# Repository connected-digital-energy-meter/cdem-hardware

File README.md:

# Connected Digital Energy Meter - Hardware

TODO

## Gerber and BOM

Checkout following guides:

* [How to generate Gerber and Drill files in KiCad 5](https://support.jlcpcb.com/article/149-how-to-generate-gerber-and-drill-files-in-kicad)
* [How to generate the BOM and Centroid file from KiCAD](https://support.jlcpcb.com/article/84-how-to-generate-the-bom-and-centroid-file-from-kicad)

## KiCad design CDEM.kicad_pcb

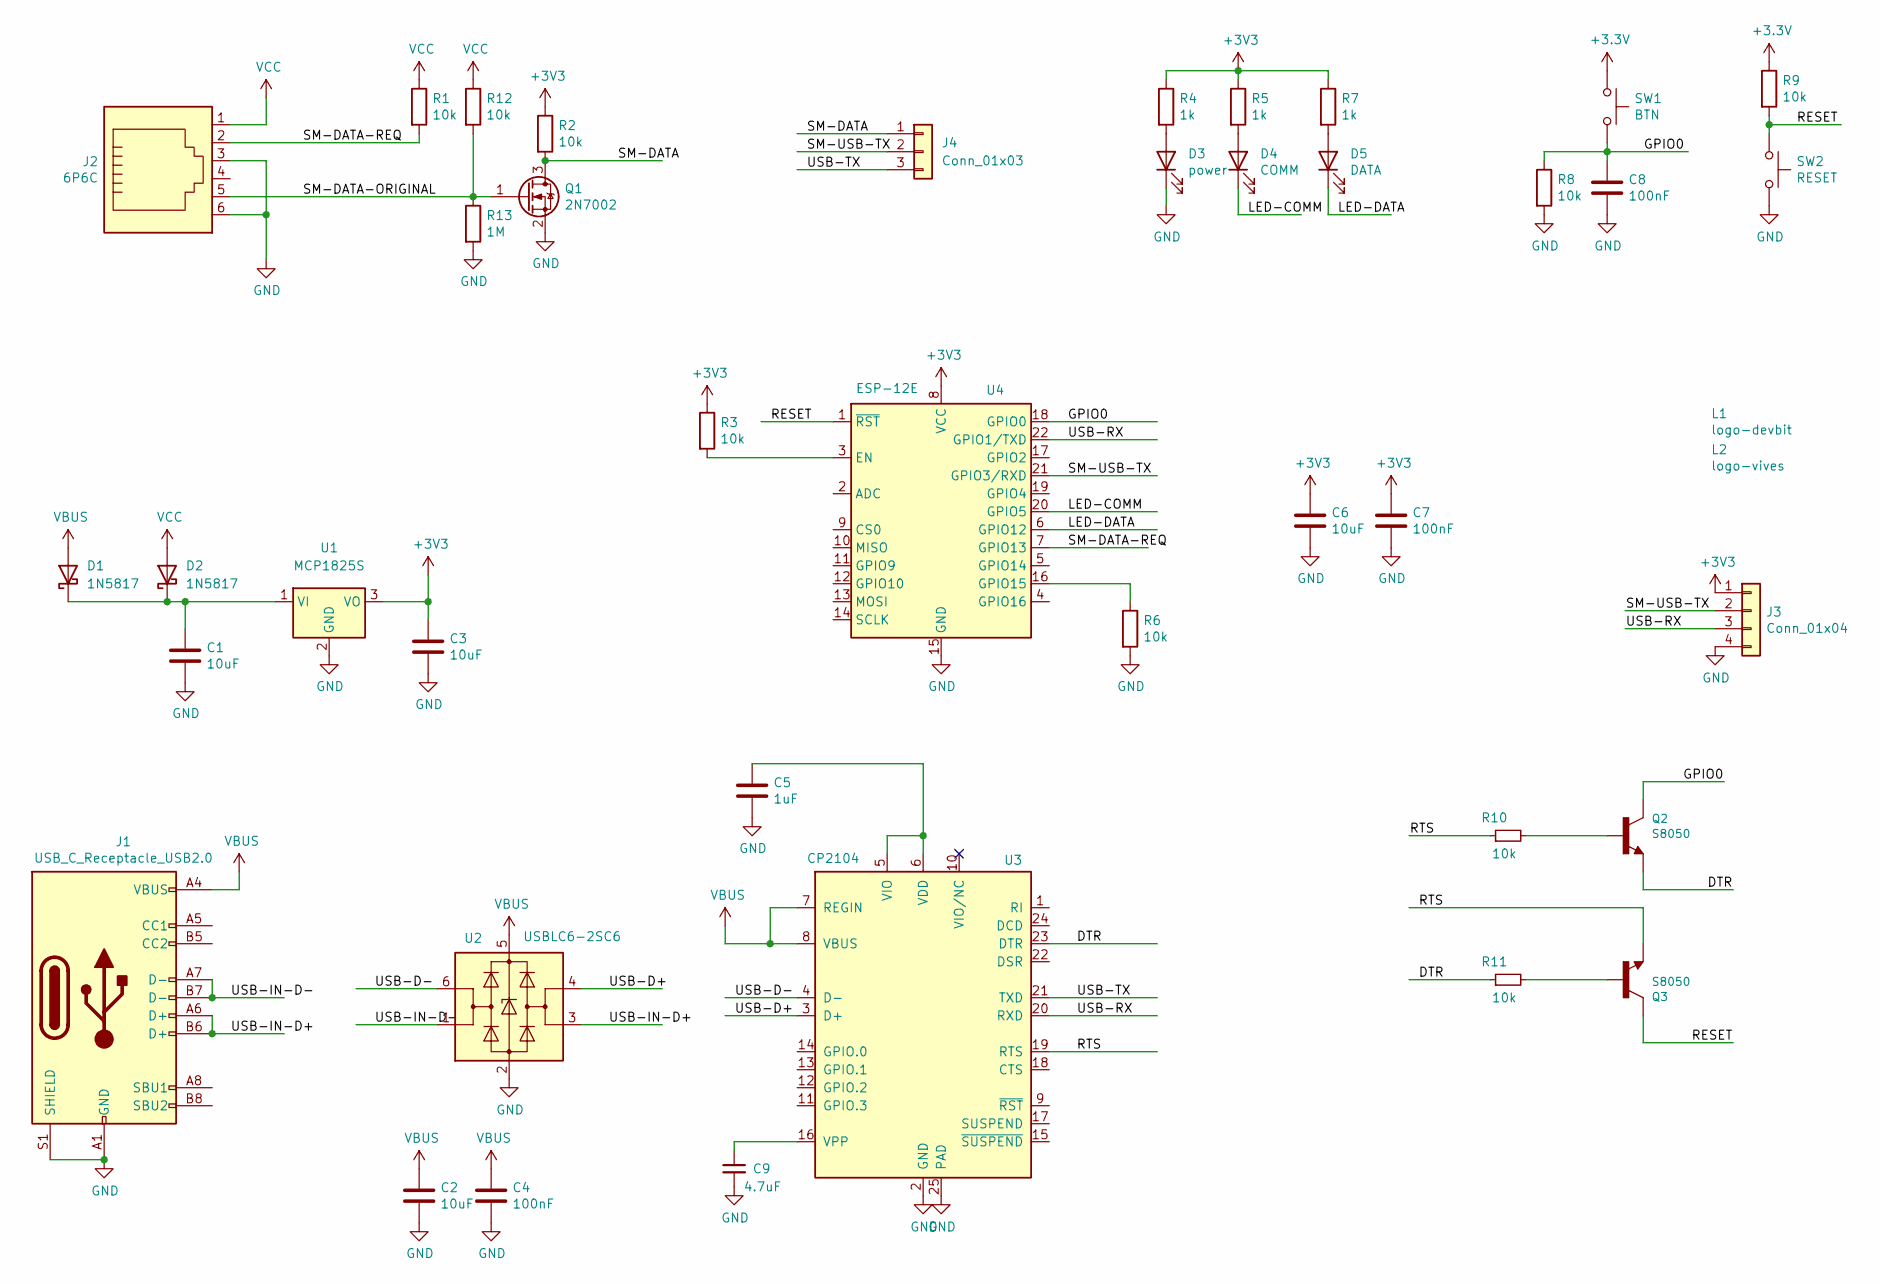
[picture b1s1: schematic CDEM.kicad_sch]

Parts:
C1, C2, C3, C6: 10uF; C_0805_2012Metric; LCSC C15850
C4, C7, C8: 100nF; C_0603_1608Metric; LCSC C14663
C5: 1uF; C_0603_1608Metric; LCSC C15849
C9: 4.7uF; C_0805_2012Metric; LCSC C1779
D1, D2: 1N5817; D_SOD-123; LCSC C727113
D3: power; LED_0603_1608Metric; LCSC C72041
D4: COMM; LED_0603_1608Metric; LCSC C72043
D5: DATA; LED_0603_1608Metric; LCSC C72038
J1: USB_C_Receptacle_USB2.0; USB_C_Receptacle_HRO_TYPE-C-31-M-12; LCSC C165948
J2: 6P6C; RJ12_Amphenol_54601; LCSC C305981
J3: Conn_01x04; PinHeader_1x04_P2.54mm_Vertical
J4: Conn_01x03; PinHeader_1x03_P2.54mm_Vertical; LCSC C390679
L1: logo-devbit; logo_devbit_8mm
L2: logo-vives; logo_vives_10mm
Q1: 2N7002; SOT-23; LCSC C8545
Q2, Q3: S8050; SOT-23; LCSC C2146
R1, R2, R3, R6, R8, R9, R10, R11, R12: 10k; R_0603_1608Metric; LCSC C25804
R4, R5, R7: 1k; R_0603_1608Metric; LCSC C21190
R13: 1M; R_0603_1608Metric; LCSC C17514
SW1: BTN; SW_SPST_B3U-1000P; LCSC C231329
SW2: RESET; SW_SPST_B3U-1000P; LCSC C231329
U1: MCP1825S; SOT-223-3_TabPin2; LCSC C145411
U2: USBLC6-2SC6; SOT-23-6; LCSC C7519
U3: CP2104; QFN-24-1EP_4x4mm_P0.5mm_EP2.6x2.6mm; LCSC C47742
U4: ESP-12E; LCSC C82898

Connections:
/DTR: Q2.2 (E), R11.1, U3.23 (DTR)
/GPIO0: C8.1, Q2.3 (C), R8.1, SW1.2, U4.18 (GPIO0)
/LED-COMM: D4.1 (K), U4.20 (GPIO5)
/LED-DATA: D5.1 (K), U4.6 (GPIO12)
/RESET: Q3.3 (C), R9.2, SW2.1, U4.1 (~RST)
/RTS: Q3.2 (E), R10.1, U3.19 (RTS)
/SM-DATA: J4.1, Q1.3 (D), R2.2
/SM-DATA-ORIGINAL: J2.5, Q1.1 (G), R12.2, R13.1
/SM-DATA-REQ: J2.2, R1.2, U4.7 (GPIO13)
/SM-USB-TX: J3.2, J4.2, U4.21 (GPIO3/RXD)
/USB-D+: U2.4 (I/O2), U3.3 (D+)
/USB-D-: U2.6 (I/O1), U3.4 (D-)
/USB-IN-D+: J1.A6 (D+), J1.B6 (D+), U2.3 (I/O2)
/USB-IN-D-: J1.A7 (D-), J1.B7 (D-), U2.1 (I/O1)
/USB-RX: J3.3, U3.20 (RXD), U4.22 (GPIO1/TXD)
/USB-TX: J4.3, U3.21 (TXD)
GND: C1.2, C2.2, C3.2, C4.2, C5.2, C6.2, C7.2, C8.2, C9.2, D3.1 (K), J1.A1 (GND), J1.A12 (GND), J1.B1 (GND), J1.B12 (GND), J1.S1 (SHIELD), J2.3, J2.6, J3.4, Q1.2 (S), R6.2, R8.2, R13.2, SW2.2, U1.2 (GND), U2.2 (GND), U3.2 (GND), U3.25 (PAD), U4.15 (GND)
unnamed: C1.1, D1.1 (K), D2.1 (K), U1.1 (VI)
unnamed: C5.1, U3.5 (VIO), U3.6 (VDD)
unnamed: C9.1, U3.16 (VPP)
unnamed: D3.2 (A), R4.2
unnamed: D4.2 (A), R5.2
unnamed: D5.2 (A), R7.2
unnamed: Q2.1 (B), R10.2
unnamed: Q3.1 (B), R11.2
unnamed: R3.2, U4.3 (EN)
unnamed: R6.1, U4.16 (GPIO15)
VBUS: C2.1, C4.1, D1.2 (A), J1.A4 (VBUS), J1.A9 (VBUS), J1.B4 (VBUS), J1.B9 (VBUS), U2.5 (VBUS), U3.7 (REGIN), U3.8 (VBUS)
VCC: D2.2 (A), J2.1, R1.1, R12.1

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
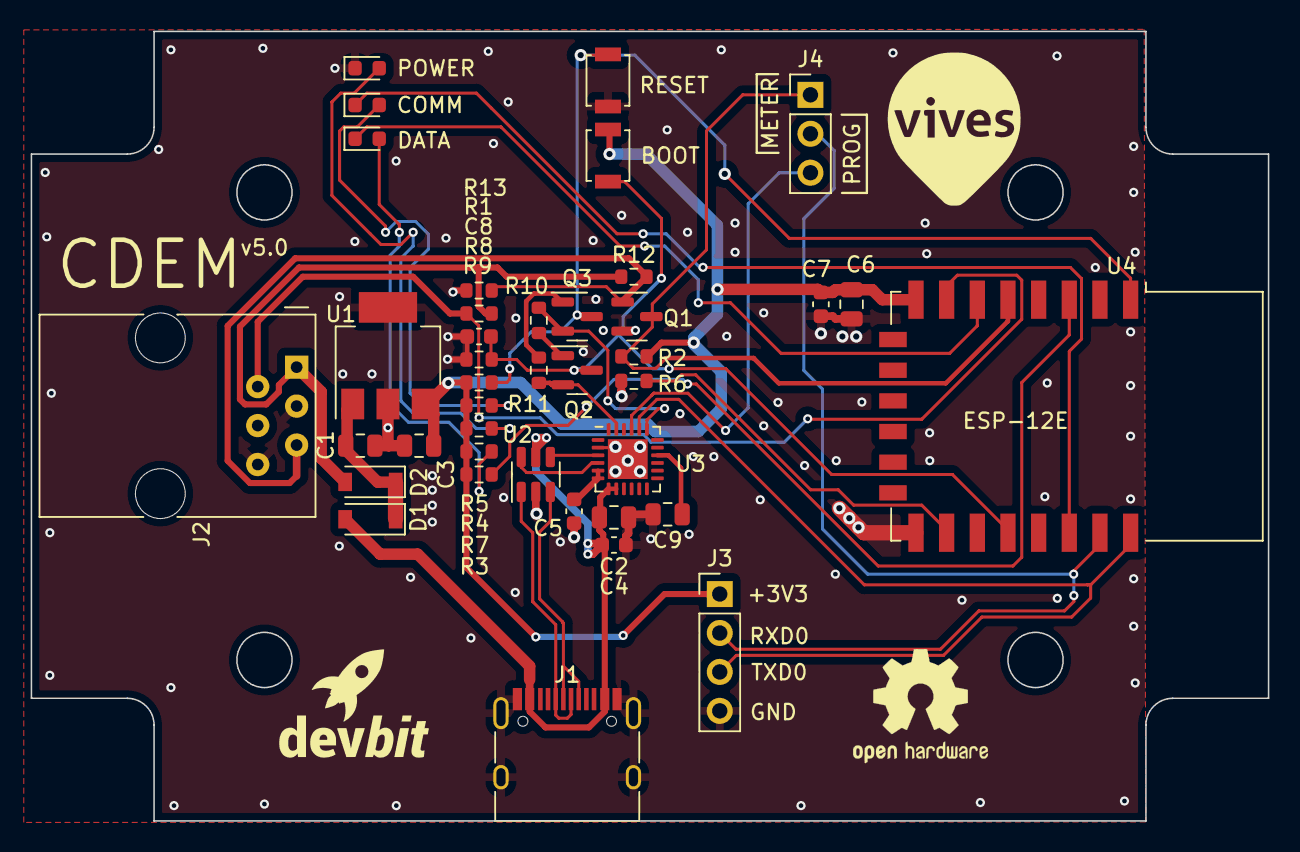
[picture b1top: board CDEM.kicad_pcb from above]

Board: 2 copper layers, 80.7 x 51.5 mm, 42 parts (0 on the bottom side), 30 nets.

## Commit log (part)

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2021-03-15 finisched routing
2021-03-15 finisching up the board
2021-03-15 add v4.0 laber on pcb
2021-03-16 generate bom and pos files
2021-03-16 final version v4.0
2021-03-30 fix power problem
2021-06-25 Replace LDO and diodes with better alternatives. Also add programming jumper
2021-08-17 Move prog jumper a bit
2021-08-17 Finalize v5.0 and generate gerber and bom files
2021-09-24 Update orientation of components
2022-06-25 fix unconnected trace to boot button
